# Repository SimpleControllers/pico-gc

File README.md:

# pico-gc

This project is based on the PhobGCC https://github.com/PhobGCC/PhobGCC-HW.  

Its drive was mainly just to see if it was possible to use the Pico dev board instead of an IC solution.  I have a full writeup here https://simplecontrollers.com/blogs/projects/pico-gc.

I don't recommend printing this board other than for educational purposes.

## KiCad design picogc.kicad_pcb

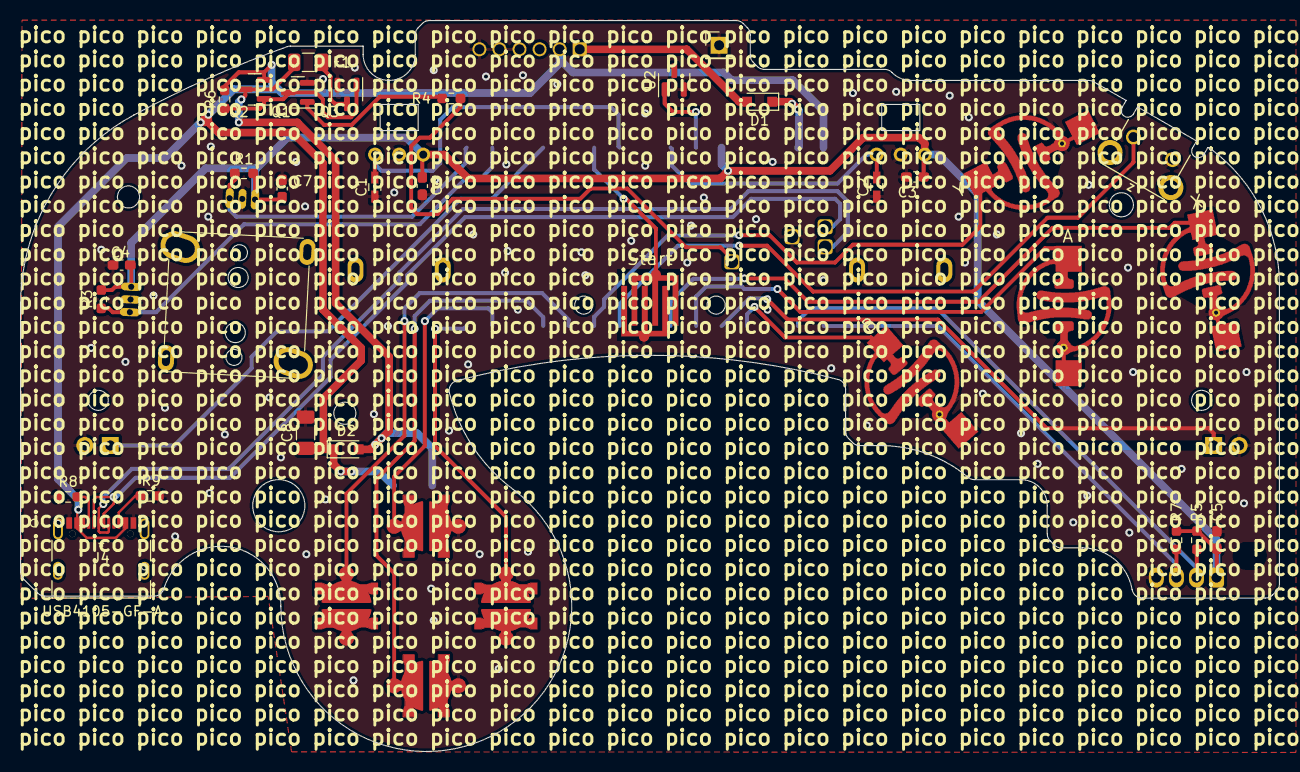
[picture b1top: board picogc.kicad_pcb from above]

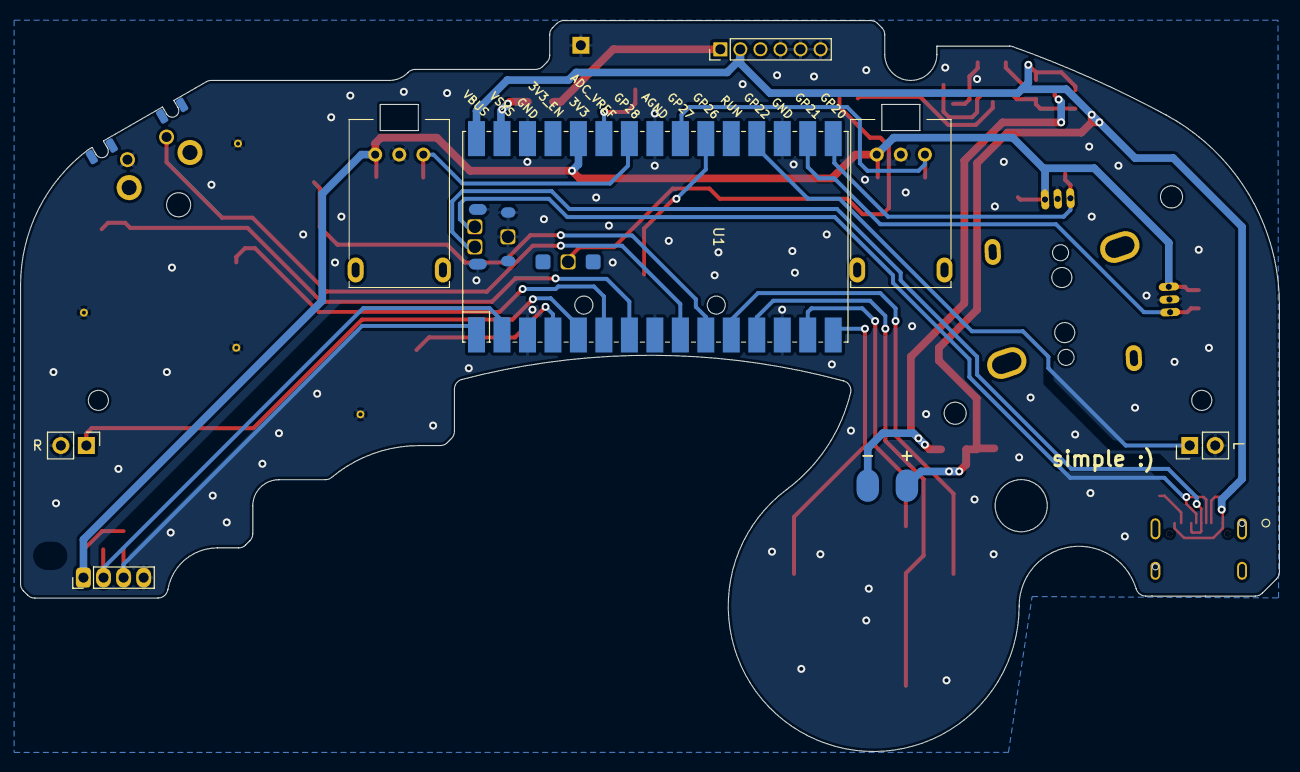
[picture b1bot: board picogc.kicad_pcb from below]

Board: 2 copper layers, 125.5 x 72.9 mm, 53 parts (8 on the bottom side), 33 nets.

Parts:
C1, C2: 0.047u; C_0603_HandSoldering
C3, C4, C5, C6, C7: 1u; C_0603_1608Metric_Pad1.08x0.95mm_HandSolder
C8: 10u; C_1206_3216Metric_Pad1.33x1.80mm_HandSolder
D1, D2: M7C; D_SOD-323_HandSoldering
F1: Fuse; Fuse_1206_3216Metric
H9: 5.2mm; MountingHole_5.2mm
H10: Slot
H11, H12: 2mm; MountingHole_2.0mm
H13, H14: 1.8mm; MountingHole_1.8mm
H15: 2.4mm; MountingHole_2.4mm
H16, H17: 2.2mm; MountingHole_2.2mm
J1: Conn_01x01_Male; PinHeader_1x01_P2.54mm_Vertical
J3: Conn_01x06_Female; GCC_Header_Straight_1x06_Pitch2.00mm
J4: USB4105-GF-A
J5: Rumble; rumble_pins
J9: Conn_01x04_Female; PinHeader_1x04_P2.00mm_Vertical
Q1, Q3: Q_NMOS_GSD; SOT-23
Q2: Q_PMOS_GDS; SOT-23
R1, R3, R5, R6, R7: 10k; R_0603_1608Metric_Pad0.98x0.95mm_HandSolder
R4: 100R; R_0603_1608Metric_Pad0.98x0.95mm_HandSolder
R8, R9: 5.1k; R_0603_1608Metric_Pad0.98x0.95mm_HandSolder
RV1, RV2: R_POT_MountingPin; GCC_Slider
SW1: Z; Z_Switch_Edge_Omron
SW2: A; ABXY_Contact_Omron_Switch
SW3: B; ABXY_Contact_Omron_Switch
SW4: X; ABXY_Contact_Omron_Switch
SW5: Y; ABXY_Contact_Omron_Switch
SW6: Start; Start_Contact
SW7: L; Pin_Header_Straight_1x02_Pitch2.54mm
SW8: R; Pin_Header_Straight_1x02_Pitch2.54mm
SW9: Dleft; Dpad_Contact_TL3315NF_2
SW10: Dup; Dpad_Contact_TL3315NF_2
SW11: Dright; Dpad_Contact_TL3315NF_2
SW12: Ddown; Dpad_Contact_TL3315NF_2
U1: Pico; RPi_Pico_SMD_MID_TRIM
U2: LM4040DBZ-3; SOT-23
U3: 2x DRV5053CAQLPGM Hall Effect Sensors; GCC_Stickbox_2

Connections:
+3.3VA: D1.2 (A), J3.1
+3V3: C3.1, C4.1, C5.1, C6.1, C7.1, J9.1, R1.2, R3.2, R5.2, R7.2, RV1.1 (V+), RV2.1 (V+), U1.36 (3V3), U3.1 (H1XV), U3.4 (H1YV)
+5V: C8.1, D2.1 (K), J3.2, J4.A4-B9 (VBUS), J4.B4-A9 (VBUS), J5.1, Q2.2 (S), R6.2, U1.40 (VBUS)
/A: SW2.1, U1.6 (GPIO4)
/B: SW3.1, U1.4 (GPIO2)
/C_x: J9.2, R5.1, U1.2 (GPIO1)
/C_y: J9.3, R7.1, U1.1 (GPIO0)
/D+: J4.A6 (DP1), J4.B6 (DP2), U1.45 (USB_DM)
/D-: J4.A7 (DN1), J4.B7 (DN2), U1.46 (USB_DP)
/Ddown: SW12.1, U1.12 (GPIO9)
/Dleft: SW9.1, U1.11 (GPIO8)
/Dright: SW11.1, U1.15 (GPIO11)
/Dup: SW10.1, U1.14 (GPIO10)
/L: SW7.1, U1.29 (GPIO22)
/Lanalog: C1.1, RV1.3 (Signal), U1.32 (GPIO27_ADC1)
/R: SW8.1, U1.5 (GPIO3)
/RUMBLE: R4.1, U1.48 (LED)
/Ranalog: C2.1, RV2.3 (Signal), U1.34 (GPIO28_ADC2)
/Start: SW6.1, U1.31 (GPIO26_ADC0)
/Stick_x: R1.1, U1.26 (GPIO20), U3.3 (H1XS)
/Stick_y: R3.1, U1.27 (GPIO21), U3.6 (H1YS)
/X: SW4.1, U1.7 (GPIO5)
/Y: SW5.1, U1.10 (GPIO7)
/Z: SW1.1, U1.9 (GPIO6)
GND: C1.2, C2.2, C3.2, C4.2, C5.2, C6.2, C7.2, C8.2, J1.1, J3.4, J3.5, J3.6, J4.A1-B12 (GND), J4.B1-A12 (GND), J9.4, Q1.2 (S), Q3.2 (S), R8.2, R9.1, RV1.2 (GND), RV2.2 (GND), SW1.2, SW2.2, SW3.2, SW4.2, SW5.2, SW6.2, SW7.2, SW8.2, SW9.2, SW10.2, SW11.2, SW12.2, U1.3 (GND), U1.8 (GND), U1.13 (GND), U1.28 (GND), U1.33 (AGND), U1.38 (GND), U1.44 (GND), U2.2 (A), U3.2 (H1XG), U3.5 (H1YG)
unnamed: D1.1 (K), U1.39 (VSYS)
unnamed: D2.2 (A), F1.1, J5.2, Q2.3 (D)
unnamed: F1.2, Q3.3 (D)
unnamed: J4.A5 (CC1), R8.1
unnamed: J4.B5 (CC2), R9.2
unnamed: Q1.1 (G), R4.2
unnamed: Q1.3 (D), Q2.1 (G), Q3.1 (G), R6.1
unnamed: U1.35 (ADC_VREF), U2.1 (K)

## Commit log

2022-08-08 Add files via upload
    Pico GC Rev1

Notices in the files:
parts and their libraries:
Copyright 2021 Accelerated Designs. All rights reserved.
